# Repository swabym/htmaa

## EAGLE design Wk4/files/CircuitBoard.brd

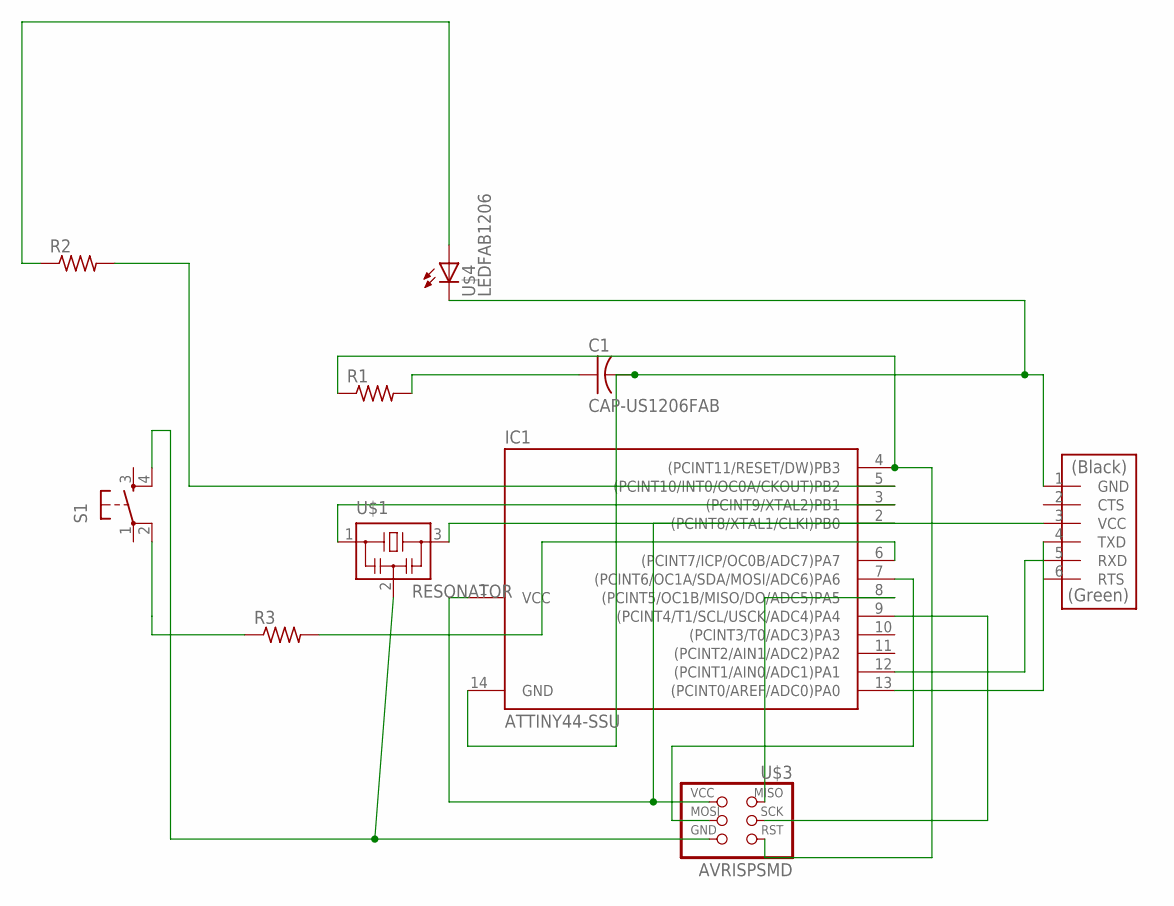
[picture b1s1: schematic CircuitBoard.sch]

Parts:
C1: CAP-US1206FAB; C1206FAB
IC1: ATTINY44-SSU; SOIC14
R1, R2, R3: RES-US1206FAB; R1206FAB
S1: 6MM_SWITCH6MM_SWITCH; 6MM_SWITCH
U$1: RESONATOR; EFOBM
U$2: FTDI-SMD-HEADER; 1X06SMD
U$3: AVRISPSMD; 2X03SMD
U$4: LEDFAB1206; LED1206FAB

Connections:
unnamed: S1.4 (S1), U$1.2, U$3.6 (GND)
unnamed: IC1.7 ((PCINT6/OC1A/SDA/MOSI/ADC6)PA6), U$3.4 (MOSI)
unnamed: IC1.1 (VCC), U$2.3 (VCC), U$3.2 (VCC)
unnamed: IC1.8 ((PCINT5/OC1B/MISO/DO/ADC5)PA5), U$3.1 (MISO)
unnamed: IC1.9 ((PCINT4/T1/SCL/USCK/ADC4)PA4), U$3.3 (SCK)
unnamed: IC1.4 ((PCINT11/RESET/DW)PB3), R1.1, U$3.5 (RST)
unnamed: IC1.3 ((PCINT9/XTAL2)PB1), U$1.1
unnamed: IC1.2 ((PCINT8/XTAL1/CLKI)PB0), U$1.3
unnamed: C1.1, R1.2
unnamed: C1.2, IC1.14 (GND), U$2.1 (GND), U$4.2 (C)
unnamed: IC1.12 ((PCINT1/AIN0/ADC1)PA1), U$2.5 (RXD)
unnamed: IC1.13 ((PCINT0/AREF/ADC0)PA0), U$2.4 (TXD)
unnamed: IC1.5 ((PCINT10/INT0/OC0A/CKOUT)PB2), R2.2
unnamed: R2.1, U$4.1 (A)
unnamed: IC1.6 ((PCINT7/ICP/OC0B/ADC7)PA7), R3.2
unnamed: R3.1, S1.2 (P1)

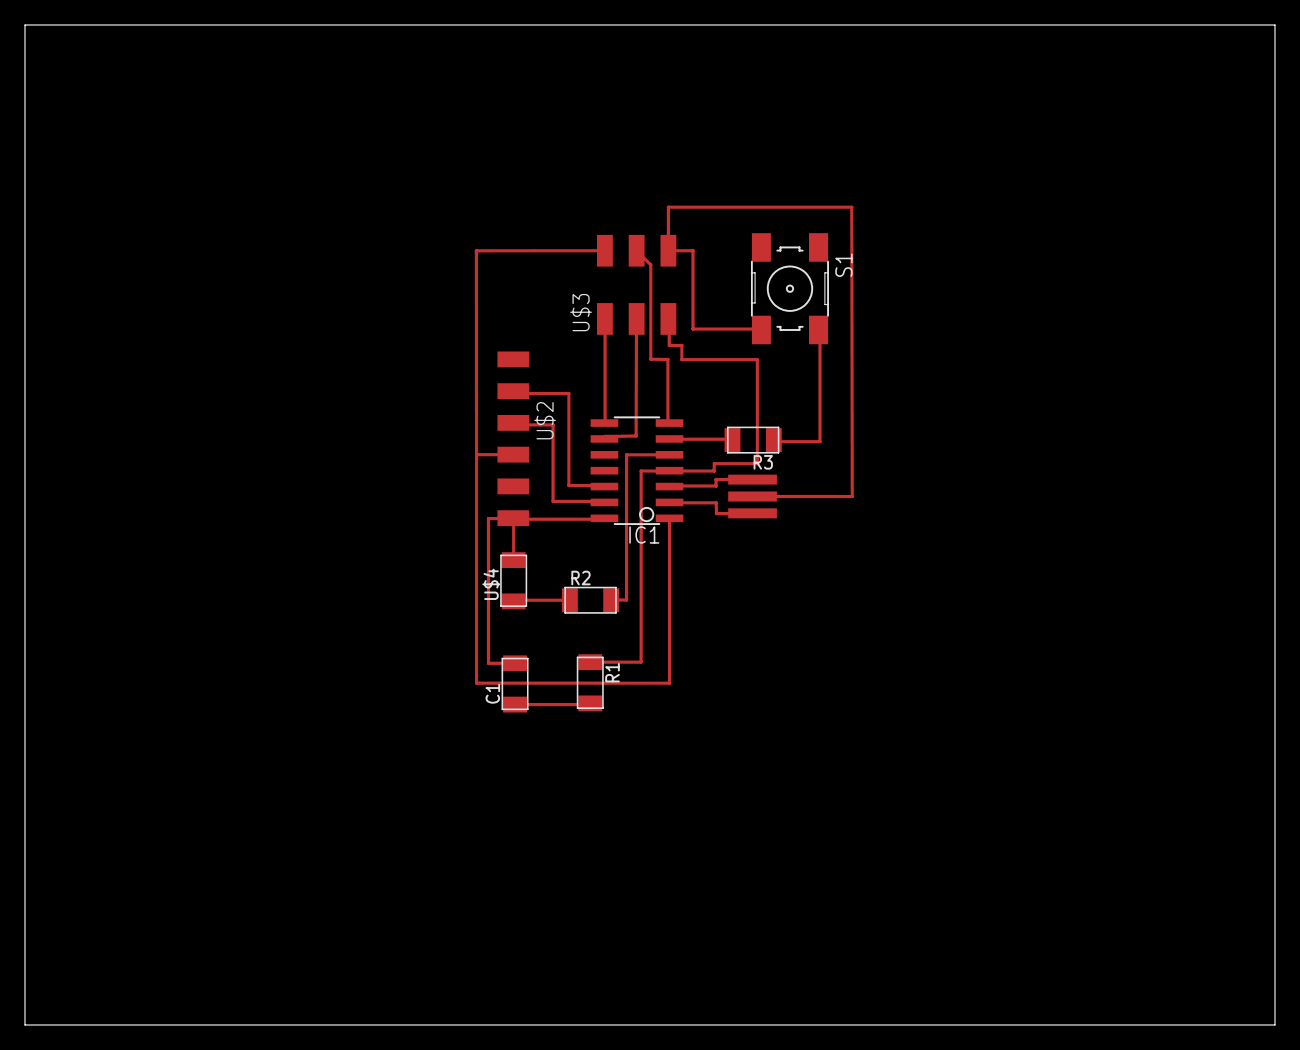
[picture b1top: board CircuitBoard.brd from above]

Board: 2 copper layers, 100.0 x 80.0 mm, 10 parts (0 on the bottom side), 16 nets.

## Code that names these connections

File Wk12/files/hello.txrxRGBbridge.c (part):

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#define led_port PORTA
#define led_direction DDRA
#define red (1 << PA2)
#define green (1 << PA0)
#define blue (1 << PA1)
//#define button_port PORTA
//#define button (1 << PAO)

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//this is for serial connection to the python script
//#define serial_port PORTB
//#define serial_direction DDRB
//#define serial_pin_out (1 << PB1)
#define transmit_port PORTA
#define transmit_direction DDRA
#define transmit_pin (1 << PA4)

//bus.44
//#define output(directions,pin) (directions |= pin) // set port direction for output
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//commented out because I used an rgb led and port specifics are above
//#define led_port PORTB
//#define led_direction DDRB
//#define led_pin (1 << PB0)

#define serial_port PORTB
#define serial_direction DDRB
#define serial_pins PINB
#define serial_pin_in (1 << PB1)
#define serial_pin_out (1 << PB0)

#define node_id '0'

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   //
  
   ADMUX = (0 << REFS1) | (0 << REFS0) // Vcc ref
      | (0 << MUX5) | (0 << MUX4) | (0 << MUX3) | (1 << MUX2) | (1 << MUX1) | (1 << MUX0); // PA7
   ADCSRA = (1 << ADEN) // enable
      | (1 << ADPS2) | (1 << ADPS1) | (0 << ADPS0); // prescaler /128
   //
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
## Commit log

2016-09-23 index.html
2016-09-29 Update css link
2016-09-29 Demo proposed project page as sample_page
